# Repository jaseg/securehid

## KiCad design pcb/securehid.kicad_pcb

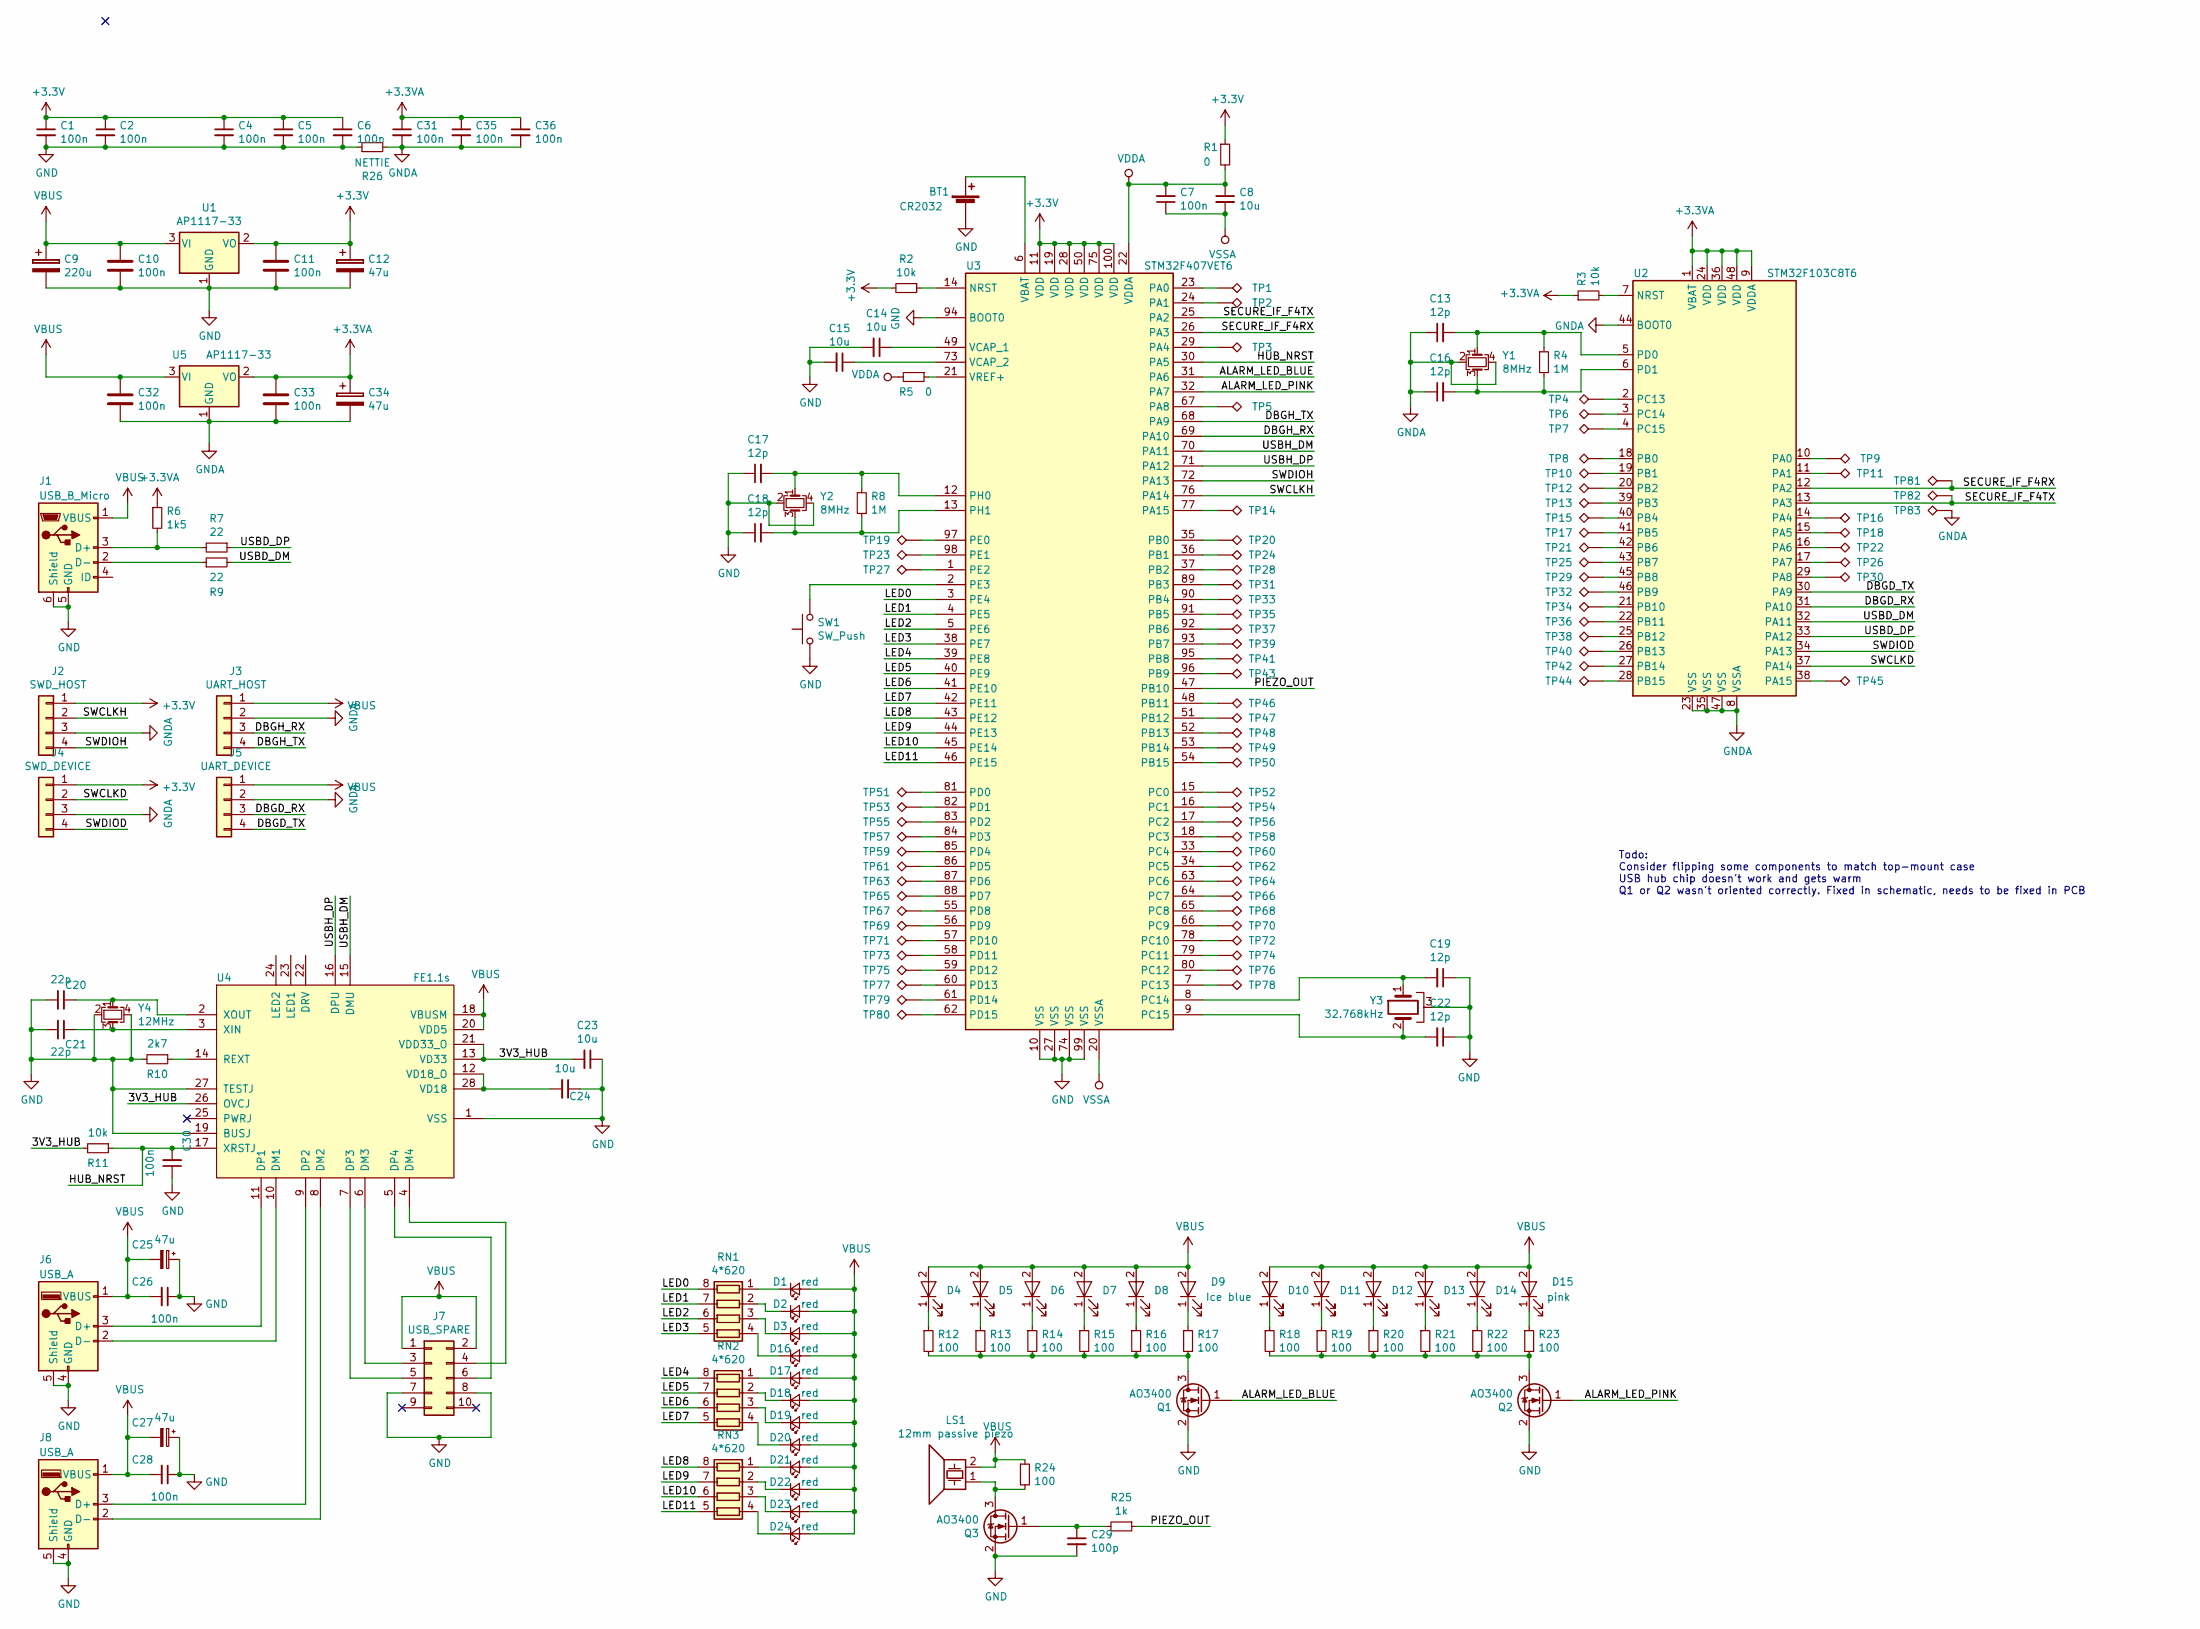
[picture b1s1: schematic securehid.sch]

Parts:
BT1: CR2032; BatteryHolder_Keystone_1060_1x2032
C1, C2, C4, C5, C6, C7, C10, C11, C26, C28, C30, C31, C32, C33, C35, C36: 100n; C_0603_1608Metric_Pad1.05x0.95mm_HandSolder
C8, C14, C15, C23, C24: 10u; C_0603_1608Metric_Pad1.05x0.95mm_HandSolder
C9: 220u; C_Elec_10x10.2
C12, C25, C27, C34: 47u; C_Elec_6.3x5.8
C13, C16, C17, C18, C19, C22: 12p; C_0603_1608Metric_Pad1.05x0.95mm_HandSolder
C20, C21: 22p; C_0603_1608Metric_Pad1.05x0.95mm_HandSolder
C29: 100p; C_0603_1608Metric_Pad1.05x0.95mm_HandSolder
D1, D2, D3, D16, D17, D18, D19, D20, D21, D22, D23, D24: red; LED_0603_1608Metric_Pad1.05x0.95mm_HandSolder
D4, D5, D6, D7, D8, D9: Ice blue; LED_PLCC_2835_Handsoldering
D10, D11, D12, D13, D14, D15: pink; LED_PLCC_2835_Handsoldering
J1: USB_B_Micro; microusb_ali_dovetail
J2: SWD_HOST; PinHeader_1x04_P2.54mm_Vertical
J3: UART_HOST; PinHeader_1x04_P2.54mm_Vertical
J4: SWD_DEVICE; PinHeader_1x04_P2.54mm_Vertical
J5: UART_DEVICE; PinHeader_1x04_P2.54mm_Vertical
J6, J8: USB_A; USB_A_FEMALE_THT
J7: USB_SPARE; PinHeader_2x05_P2.54mm_Vertical
LS1: 12mm passive piezo; Buzzer_12x9.5RM7.6
Q1, Q2, Q3: AO3400; SOT-23
R1, R5: 0; R_0603_1608Metric_Pad1.05x0.95mm_HandSolder
R2, R3, R11: 10k; R_0603_1608Metric_Pad1.05x0.95mm_HandSolder
R4, R8: 1M; R_0603_1608Metric_Pad1.05x0.95mm_HandSolder
R6: 1k5; R_0603_1608Metric_Pad1.05x0.95mm_HandSolder
R7, R9: 22; R_0603_1608Metric_Pad1.05x0.95mm_HandSolder
R10: 2k7; R_0603_1608Metric_Pad1.05x0.95mm_HandSolder
R12, R13, R14, R15, R16, R17, R18, R19, R20, R21, R22, R23, R24: 100; R_0603_1608Metric_Pad1.05x0.95mm_HandSolder
R25: 1k; R_0603_1608Metric_Pad1.05x0.95mm_HandSolder
R26: NETTIE; NetTie-2_SMD_Pad2.0mm
RN1, RN2, RN3: 4*620; R_Array_Convex_4x0603
SW1: SW_Push; SW_SPST_EVPBF
TP1, TP2, TP3, TP4, TP5, TP6, TP7, TP8, TP9, TP10, TP11, TP12, TP13, TP14, TP15, TP16, TP17, TP18, TP19, TP20, TP21, TP22, TP23, TP24, TP25, TP26, TP27, TP28, TP29, TP30, TP31, TP32, TP33, TP34, TP35, TP36, TP37, TP38, TP39, TP40, TP41, TP42, TP43, TP44, TP45, TP46, TP47, TP48, TP49, TP50, TP51, TP52, TP53, TP54, TP55, TP56, TP57, TP58, TP59, TP60, TP61, TP62, TP63, TP64, TP65, TP66, TP67, TP68, TP69, TP70, TP71, TP72, TP73, TP74, TP75, TP76, TP77, TP78, TP79, TP80, TP81, TP82, TP83: TestPoint_Alt; TestPoint_Pad_1.0x1.0mm
U1, U5: AP1117-33; SOT-223-3Lead_TabPin2
U2: STM32F103C8T6; LQFP-48_7x7mm_P0.5mm
U3: STM32F407VET6; LQFP-100_14x14mm_P0.5mm
U4: FE1.1s; SSOP-28_3.9x9.9mm_P0.635mm
Y1, Y2: 8MHz; Crystal_SMD_TXC_7M-4Pin_3.2x2.5mm_HandSoldering
Y3: 32.768kHz; Crystal_C26-LF_D2.1mm_L6.5mm_Horizontal_1EP_style1
Y4: 12MHz; Crystal_SMD_TXC_7M-4Pin_3.2x2.5mm_HandSoldering

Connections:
+3.3VA: C31.1, C33.1, C34.1, C35.1, C36.1, R3.1, R6.1, U2.1 (VBAT), U2.9 (VDDA), U2.24 (VDD), U2.36 (VDD), U2.48 (VDD), U5.2 (VO)
+3V3: C1.1, C2.1, C4.1, C5.1, C6.1, C11.1, C12.1, J2.1, J4.1, R1.1, R2.2, U1.2 (VO), U3.11 (VDD), U3.19 (VDD), U3.28 (VDD), U3.50 (VDD), U3.75 (VDD), U3.100 (VDD)
/3V3_HUB: C23.2, R11.2, U4.13 (VD33), U4.21 (VDD33_O), U4.26 (OVCJ)
/ALARM_LED_BLUE: Q1.1 (G), U3.31 (PA6)
/ALARM_LED_PINK: Q2.1 (G), U3.32 (PA7)
/DBGD_RX: J5.3, U2.31 (PA10)
/DBGD_TX: J5.4, U2.30 (PA9)
/DBGH_RX: J3.3, U3.69 (PA10)
/DBGH_TX: J3.4, U3.68 (PA9)
/HUB_NRST: C30.2, R11.1, U3.30 (PA5), U4.17 (XRSTJ)
/LED0: RN1.8 (R1.2), U3.3 (PE4)
/LED1: RN1.7 (R2.2), U3.4 (PE5)
/LED2: RN1.6 (R3.2), U3.5 (PE6)
/LED3: RN1.5 (R4.2), U3.38 (PE7)
/LED4: RN2.8 (R1.2), U3.39 (PE8)
/LED5: RN2.7 (R2.2), U3.40 (PE9)
/LED6: RN2.6 (R3.2), U3.41 (PE10)
/LED7: RN2.5 (R4.2), U3.42 (PE11)
/LED8: RN3.8 (R1.2), U3.43 (PE12)
/LED9: RN3.7 (R2.2), U3.44 (PE13)
/LED10: RN3.6 (R3.2), U3.45 (PE14)
/LED11: RN3.5 (R4.2), U3.46 (PE15)
/PIEZO_OUT: R25.1, U3.47 (PB10)
/SECURE_IF_F4RX: TP81.1, U2.12 (PA2), U3.26 (PA3)
/SECURE_IF_F4TX: TP82.1, U2.13 (PA3), U3.25 (PA2)
/SWCLKD: J4.2, U2.37 (PA14)
/SWCLKH: J2.2, U3.76 (PA14)
/SWDIOD: J4.4, U2.34 (PA13)
/SWDIOH: J2.4, U3.72 (PA13)
/USBD_DM: R9.2, U2.32 (PA11)
/USBD_DP: R7.1, U2.33 (PA12)
/USBH_DM: U3.70 (PA11), U4.15 (DMU)
/USBH_DP: U3.71 (PA12), U4.16 (DPU)
GNDA: C13.1, C16.1, C31.2, C32.2, C33.2, C34.2, C35.2, C36.2, J2.3, J3.2, J4.3, J5.2, R26.2, TP83.1, U2.8 (VSSA), U2.23 (VSS), U2.35 (VSS), U2.44 (BOOT0), U2.47 (VSS), U5.1 (GND), Y1.2, Y1.4
unnamed: BT1.1 (+), U3.6 (VBAT)
unnamed: C13.2, R4.1, U2.5 (PD0), Y1.1
unnamed: C14.1, U3.49 (VCAP_1)
unnamed: C15.1, U3.73 (VCAP_2)
unnamed: C16.2, R4.2, U2.6 (PD1), Y1.3
unnamed: C17.2, R8.1, U3.12 (PH0), Y2.1
unnamed: C18.2, R8.2, U3.13 (PH1), Y2.3
unnamed: C19.2, U3.8 (PC14), Y3.1
unnamed: C20.1, U4.2 (XOUT), Y4.1
unnamed: C21.1, U4.3 (XIN), Y4.3
unnamed: C22.2, U3.9 (PC15), Y3.2
unnamed: C24.2, U4.12 (VD18_O), U4.28 (VD18)
unnamed: C29.1, Q3.1 (G), R25.2
unnamed: D1.1 (K), RN1.1 (R1.1)
unnamed: D2.1 (K), RN1.2 (R2.1)
unnamed: D3.1 (K), RN1.3 (R3.1)
unnamed: D4.1 (K), R12.1
unnamed: D5.1 (K), R13.1
unnamed: D6.1 (K), R14.1
unnamed: D7.1 (K), R15.1
unnamed: D8.1 (K), R16.1
unnamed: D9.1 (K), R17.1
unnamed: D10.1 (K), R18.1
unnamed: D11.1 (K), R19.1
unnamed: D12.1 (K), R20.1
unnamed: D13.1 (K), R21.1
unnamed: D14.1 (K), R22.1
unnamed: D15.1 (K), R23.1
unnamed: D16.1 (K), RN1.4 (R4.1)
unnamed: D17.1 (K), RN2.1 (R1.1)
unnamed: D18.1 (K), RN2.2 (R2.1)
unnamed: D19.1 (K), RN2.3 (R3.1)
unnamed: D20.1 (K), RN2.4 (R4.1)
unnamed: D21.1 (K), RN3.1 (R1.1)
unnamed: D22.1 (K), RN3.2 (R2.1)
unnamed: D23.1 (K), RN3.3 (R3.1)
unnamed: D24.1 (K), RN3.4 (R4.1)
unnamed: J1.2 (D-), R9.1
unnamed: J1.3 (D+), R6.2, R7.2
unnamed: J6.2 (D-), U4.10 (DM1)
unnamed: J6.3 (D+), U4.11 (DP1)
unnamed: J7.3, U4.6 (DM3)
unnamed: J7.4, U4.4 (DM4)
unnamed: J7.5, U4.7 (DP3)
unnamed: J7.6, U4.5 (DP4)
unnamed: J8.2 (D-), U4.8 (DM2)
unnamed: J8.3 (D+), U4.9 (DP2)
unnamed: LS1.1, Q3.3 (D), R24.2
unnamed: Q1.3 (D), R12.2, R13.2, R14.2, R15.2, R16.2, R17.2
unnamed: R2.1, U3.14 (NRST)
unnamed: R3.2, U2.7 (NRST)
unnamed: R5.1, U3.21 (VREF+)
unnamed: R10.1, U4.14 (REXT)
unnamed: SW1.2, U3.2 (PE3)
unnamed: TP1.1, U3.23 (PA0)
unnamed: TP2.1, U3.24 (PA1)
unnamed: TP3.1, U3.29 (PA4)
unnamed: TP4.1, U2.2 (PC13)
unnamed: TP5.1, U3.67 (PA8)
unnamed: TP6.1, U2.3 (PC14)
unnamed: TP7.1, U2.4 (PC15)
unnamed: TP8.1, U2.18 (PB0)
unnamed: TP9.1, U2.10 (PA0)
unnamed: TP10.1, U2.19 (PB1)
unnamed: TP11.1, U2.11 (PA1)
unnamed: TP12.1, U2.20 (PB2)
unnamed: TP13.1, U2.39 (PB3)
unnamed: TP14.1, U3.77 (PA15)
unnamed: TP15.1, U2.40 (PB4)
unnamed: TP16.1, U2.14 (PA4)
unnamed: TP17.1, U2.41 (PB5)
unnamed: TP18.1, U2.15 (PA5)
unnamed: TP19.1, U3.97 (PE0)
unnamed: TP20.1, U3.35 (PB0)
unnamed: TP21.1, U2.42 (PB6)
unnamed: TP22.1, U2.16 (PA6)
unnamed: TP23.1, U3.98 (PE1)
unnamed: TP24.1, U3.36 (PB1)
unnamed: TP25.1, U2.43 (PB7)
unnamed: TP26.1, U2.17 (PA7)
unnamed: TP27.1, U3.1 (PE2)
unnamed: TP28.1, U3.37 (PB2)
unnamed: TP29.1, U2.45 (PB8)
unnamed: TP30.1, U2.29 (PA8)
unnamed: TP31.1, U3.89 (PB3)
unnamed: TP32.1, U2.46 (PB9)
unnamed: TP33.1, U3.90 (PB4)
unnamed: TP34.1, U2.21 (PB10)
unnamed: TP35.1, U3.91 (PB5)
unnamed: TP36.1, U2.22 (PB11)
unnamed: TP37.1, U3.92 (PB6)
unnamed: TP38.1, U2.25 (PB12)
unnamed: TP39.1, U3.93 (PB7)
unnamed: TP40.1, U2.26 (PB13)
unnamed: TP41.1, U3.95 (PB8)
unnamed: TP42.1, U2.27 (PB14)
unnamed: TP43.1, U3.96 (PB9)
unnamed: TP44.1, U2.28 (PB15)
unnamed: TP45.1, U2.38 (PA15)
unnamed: TP46.1, U3.48 (PB11)
unnamed: TP47.1, U3.51 (PB12)
unnamed: TP48.1, U3.52 (PB13)
unnamed: TP49.1, U3.53 (PB14)
unnamed: TP50.1, U3.54 (PB15)
unnamed: TP51.1, U3.81 (PD0)
unnamed: TP52.1, U3.15 (PC0)
unnamed: TP53.1, U3.82 (PD1)
unnamed: TP54.1, U3.16 (PC1)
unnamed: TP55.1, U3.83 (PD2)
unnamed: TP56.1, U3.17 (PC2)
unnamed: TP57.1, U3.84 (PD3)
unnamed: TP58.1, U3.18 (PC3)
unnamed: TP59.1, U3.85 (PD4)
unnamed: TP60.1, U3.33 (PC4)
unnamed: TP61.1, U3.86 (PD5)
unnamed: TP62.1, U3.34 (PC5)
unnamed: TP63.1, U3.87 (PD6)
unnamed: TP64.1, U3.63 (PC6)
unnamed: TP65.1, U3.88 (PD7)
unnamed: TP66.1, U3.64 (PC7)
unnamed: TP67.1, U3.55 (PD8)
unnamed: TP68.1, U3.65 (PC8)
unnamed: TP69.1, U3.56 (PD9)
unnamed: TP70.1, U3.66 (PC9)
unnamed: TP71.1, U3.57 (PD10)
unnamed: TP72.1, U3.78 (PC10)
unnamed: TP73.1, U3.58 (PD11)
unnamed: TP74.1, U3.79 (PC11)
unnamed: TP75.1, U3.59 (PD12)
unnamed: TP76.1, U3.80 (PC12)
unnamed: TP77.1, U3.60 (PD13)
unnamed: TP78.1, U3.7 (PC13)
unnamed: TP79.1, U3.61 (PD14)
unnamed: TP80.1, U3.62 (PD15)
VBUS: C9.1, C10.1, C25.2, C26.2, C27.2, C28.2, C32.1, D1.2 (A), D2.2 (A), D3.2 (A), D4.2 (A), D5.2 (A), D6.2 (A), D7.2 (A), D8.2 (A), D9.2 (A), D10.2 (A), D11.2 (A), D12.2 (A), D13.2 (A), D14.2 (A), D15.2 (A), D16.2 (A), D17.2 (A), D18.2 (A), D19.2 (A), D20.2 (A), D21.2 (A), D22.2 (A), D23.2 (A), D24.2 (A), J1.1 (VBUS), J3.1, J5.1, J6.1 (VBUS), J7.1, J7.2, J8.1 (VBUS), LS1.2, R24.1, U1.3 (VI), U4.18 (VBUSM), U4.20 (VDD5), U5.3 (VI)
VDDA: C7.2, C8.1, R1.2, R5.2, U3.22 (VDDA)
VSSA: C7.1, C8.2, U3.20 (VSSA)

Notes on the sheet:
Todo: Consider flipping some components to match top-mount case USB hub chip doesn't work and gets warm Q1 or Q2 wasn't oriented correctly. Fixed in schematic, needs to be fixed in PCB

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
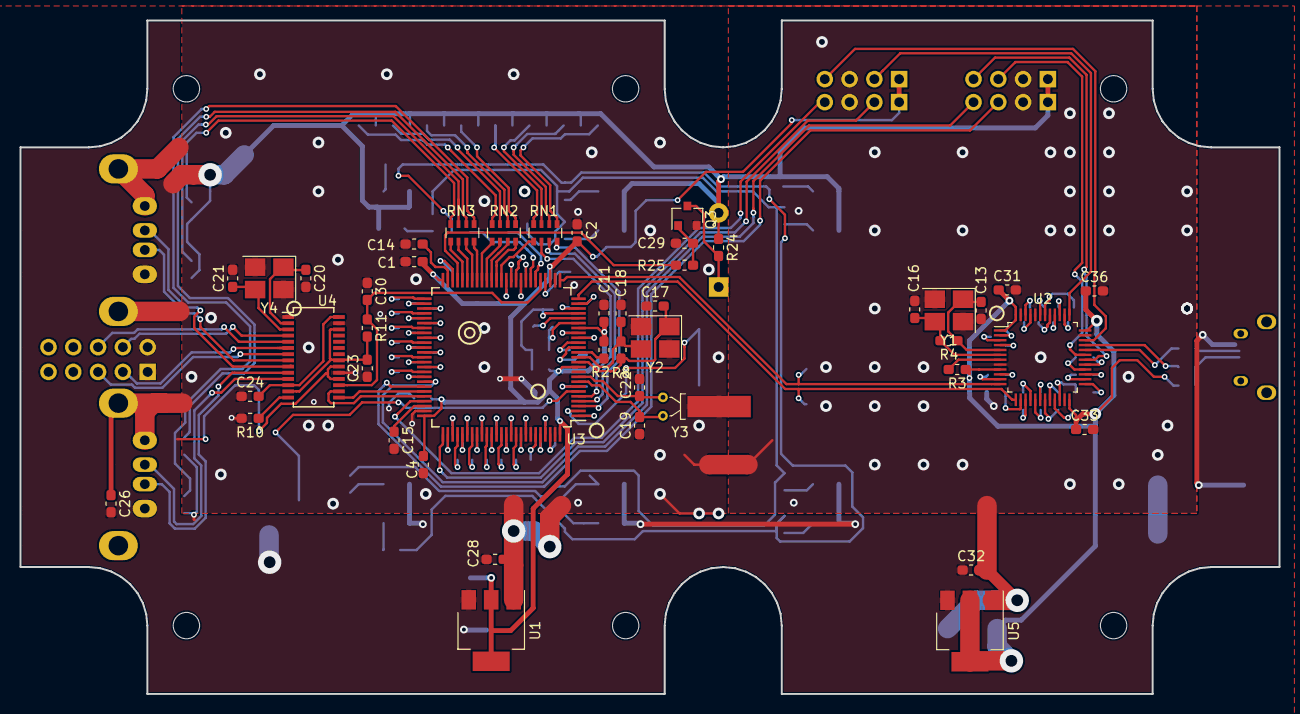
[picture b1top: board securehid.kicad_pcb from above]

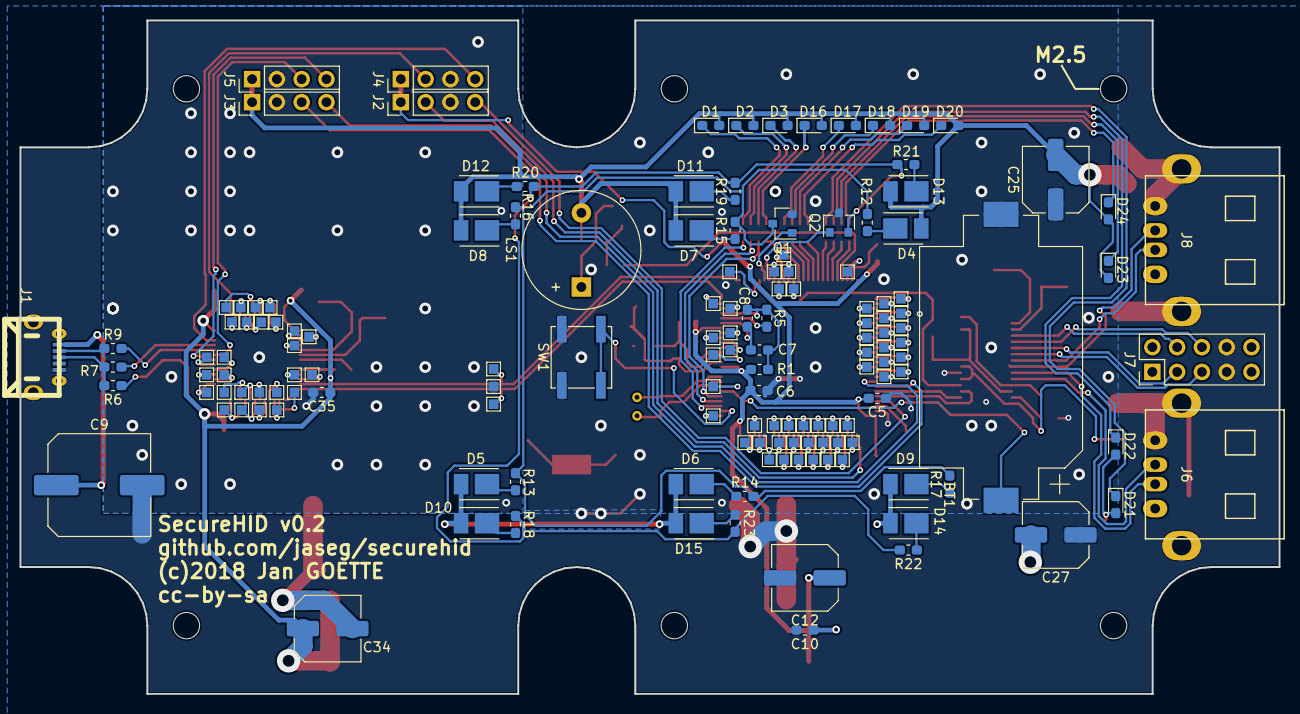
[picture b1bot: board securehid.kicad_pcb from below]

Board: 2 copper layers, 129.0 x 69.0 mm, 194 parts (148 on the bottom side), 173 nets.

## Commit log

2017-07-30 Initial commit, blink working
2017-07-30 USB HID host code import
2017-07-31 Boot, UART working
2018-11-17 Initial schematic commit
2018-11-19 Add old architecture documents
2018-11-21 Initial PCB draft
2018-11-21 Some cleanups
2018-11-22 Further PCB cleanup, initial silk cleanup
2018-11-22 PCB silk: hide testpoint references
2018-11-27 pcb: Add project info to silk and do gerber export
2018-11-27 pcb: Add BOM
2018-11-29 Some small fixes, add silk artwork
2018-11-29 pcb: Fix a bunch of kicady layout errors
2018-11-29 Add directions writeup
2018-11-29 Add system diagram for traditional system
2018-11-30 Add comparison table, include system diagrams
2018-12-01 lightning talk: slight slide reordering
2018-12-11 Make a really fancy diagram
2018-12-12 Make noise xx flowchart pretty
2018-12-12 More paper writing
2018-12-13 Expand text, add mouse mockup
2018-12-13 Add mouse pairing mockup
2018-12-13 Add lightning talk resources
2018-12-13 Update gitignore, add missing image
2019-02-13 paper: Add initial blurb on SSH kex foo
2019-02-13 paper: extend future work and UI foo
2019-04-22 paper: Expand usability section, general fixes
2020-07-29 Add paper preprint

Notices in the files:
pcb/securehid.kicad_pcb:
(c)2018 Jan GOETTE
cc-by-sa
